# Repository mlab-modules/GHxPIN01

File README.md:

# GHxPIN01 Module: MLAB to PixHawk xPIN interface

## Overview
The GHxPIN01 Module is a pin-header adapter that converts JST-GH connectors, commonly used in [PixHawk](https://github.com/pixhawk/Pixhawk-Standards/blob/master/DS-009%20Pixhawk%20Connector%20Standard.pdf) avionics, to standard pin headers. This module includes 3 to 10pin JST-GH connectors and supports UART, GPS or SPI bus communication, making it a versatile and essential component in the MLAB system for integrating various electronic devices.

## Features
- **User-Friendly Design**: Simplifies connections without complex modifications.
- **High Compatibility**: Integrates seamlessly with MLAB modular components.
- **Durable Construction**: High-quality materials for reliable and robust performance.

## Specifications
- **Connector JST-GH**: 4-10-pin JST-GH [PixHawk standard](https://github.com/pixhawk/Pixhawk-Standards/blob/master/DS-009%20Pixhawk%20Connector%20Standard.pdf)
- **Connector HEADER**: Standard 2.54mm pin header
- **Operating Temperature Range**: -40°C to 85°C

## Possible uses
- Integrating custom avionics into Pixhawk drone projects.
- Connecting JST-GH devices to MLAB standard pin header-based systems.
- Prototyping and development with MLAB modular components.

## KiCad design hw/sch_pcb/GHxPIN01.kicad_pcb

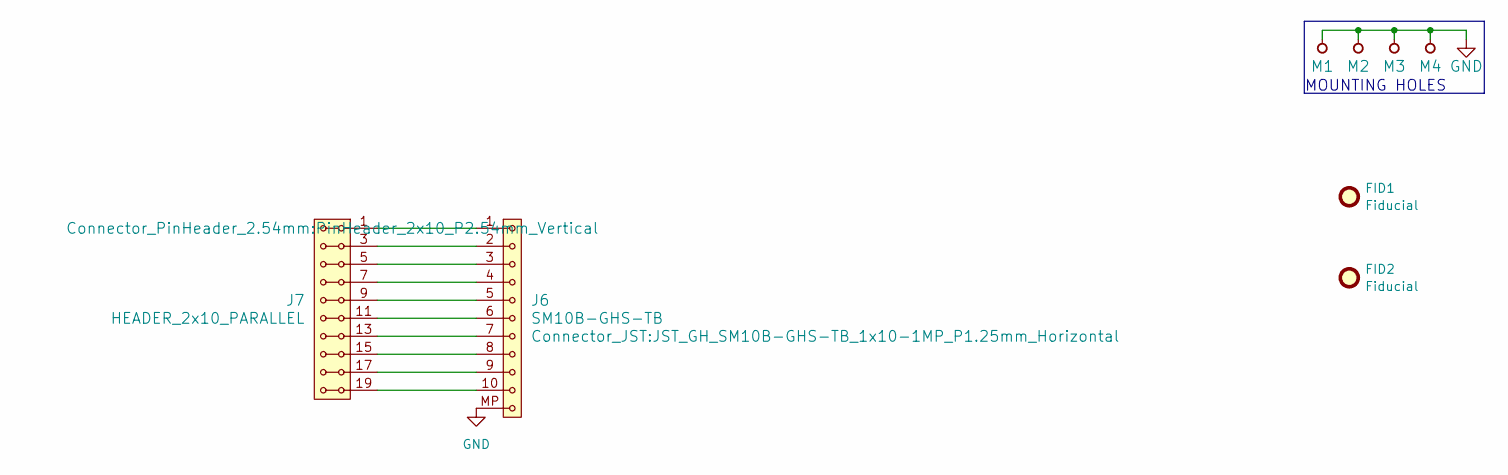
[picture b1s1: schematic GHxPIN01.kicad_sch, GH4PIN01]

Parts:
FID1, FID2: Fiducial; Fiducial_1mm_Mask2mm
J6: SM10B-GHS-TB; JST_GH_SM10B-GHS-TB_1x10-1MP_P1.25mm_Horizontal
J7: HEADER_2x10_PARALLEL; PinHeader_2x10_P2.54mm_Vertical
M1, M2: HOLE M3; MountingHole_3mm
M3, M4: HOLE; MountingHole_3mm

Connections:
GND: J6.MP, M1.1, M2.1, M3.1, M4.1
unnamed: J6.1, J7.1, J7.2
unnamed: J6.2, J7.3, J7.4
unnamed: J6.3, J7.5, J7.6
unnamed: J6.4, J7.7, J7.8
unnamed: J6.5, J7.9, J7.10
unnamed: J6.6, J7.11, J7.12
unnamed: J6.7, J7.13, J7.14
unnamed: J6.8, J7.15, J7.16
unnamed: J6.9, J7.17, J7.18
unnamed: J6.10, J7.19, J7.20

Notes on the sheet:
MOUNTING HOLES

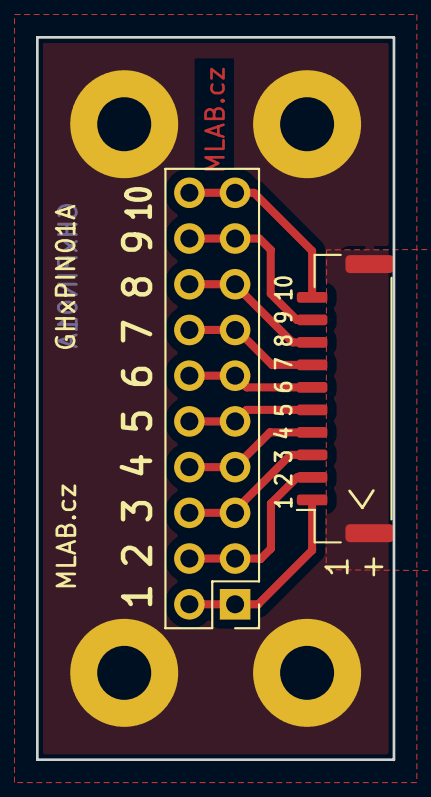
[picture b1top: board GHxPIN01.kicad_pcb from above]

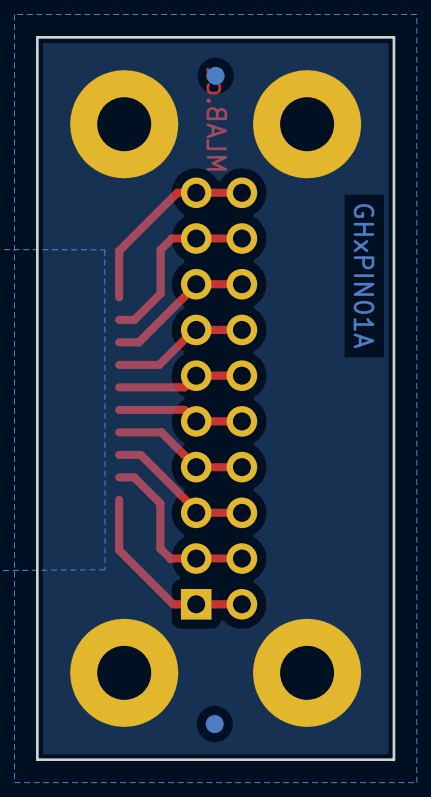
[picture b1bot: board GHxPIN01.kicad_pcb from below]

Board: 2 copper layers, 19.8 x 40.1 mm, 8 parts (2 on the bottom side), 11 nets.

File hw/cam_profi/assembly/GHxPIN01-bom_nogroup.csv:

Component,Description,Part,References,Value,Footprint,Quantity Per PCB,Datasheet
1,"2x10 2.54 mm pitch header, 2 pins next to each other are connected",HEADER_2x10_PARALLEL,J7,HEADER_2x10_PARALLEL,PinHeader_2x10_P2.54mm_Vertical,1,
2,"Zásuvka; kabel-pl.spoj; vidlice; GH; 1,25mm; PIN: 10; SMT; 50V; 1A",SM10B-GHS-TB,J6,SM10B-GHS-TB,JST_GH_SM10B-GHS-TB_1x10-1MP_P1.25mm_Horizontal,1,

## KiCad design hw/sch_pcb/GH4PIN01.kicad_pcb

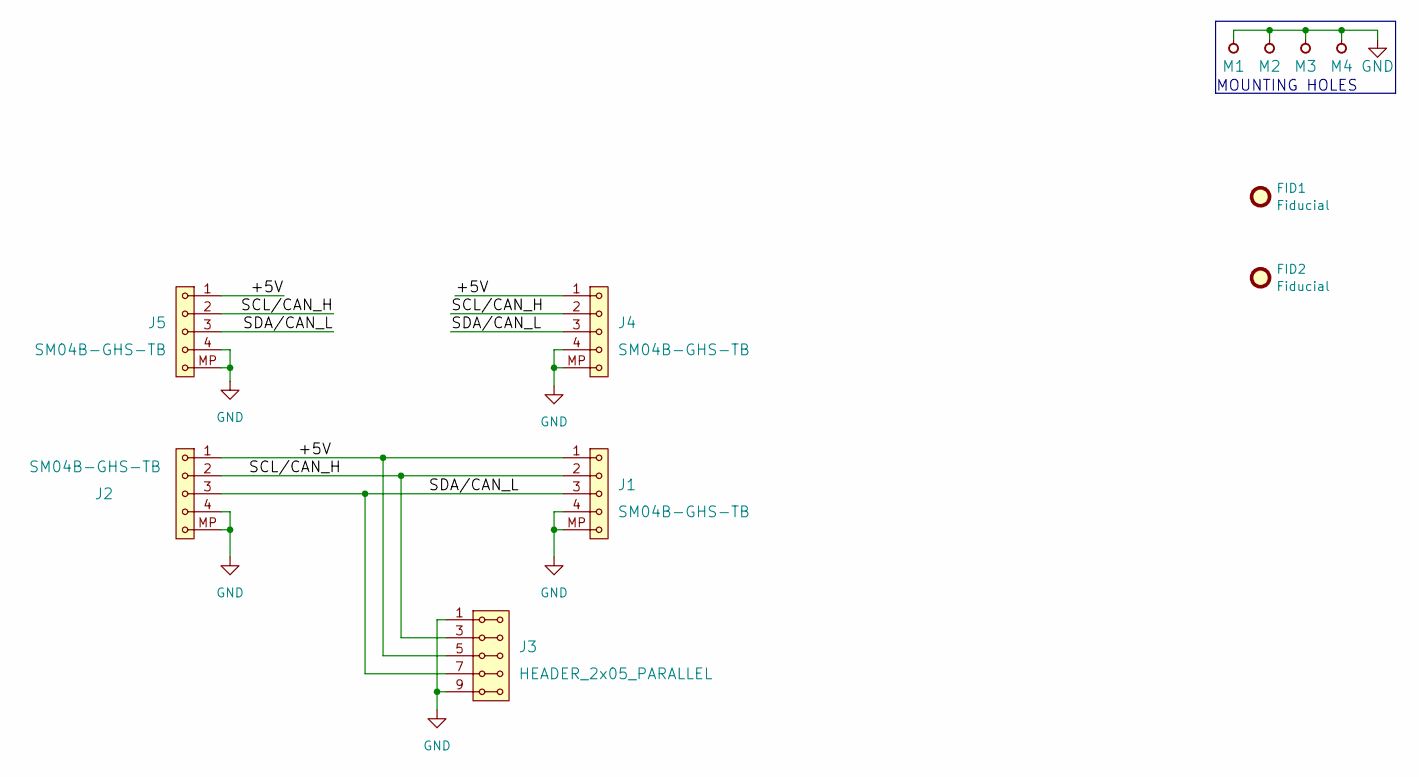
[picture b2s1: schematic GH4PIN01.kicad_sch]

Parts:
FID1, FID2: Fiducial; Fiducial_1mm_Mask2mm
J1, J2, J4, J5: SM04B-GHS-TB; JST_GH_SM04B-GHS-TB_1x04-1MP_P1.25mm_Horizontal
J3: HEADER_2x05_PARALLEL; Straight_2x05
M1, M2: HOLE M3; MountingHole_3mm
M3, M4: HOLE; MountingHole_3mm

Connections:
/+5V: J1.1, J2.1, J3.5, J3.6, J4.1, J5.1
/SCL/CAN_H: J1.2, J2.2, J3.3, J3.4, J4.2, J5.2
/SDA/CAN_L: J1.3, J2.3, J3.7, J3.8, J4.3, J5.3
GND: J1.4, J1.MP, J2.4, J2.MP, J3.1, J3.2, J3.9, J3.10, J4.4, J4.MP, J5.4, J5.MP, M1.1, M2.1, M3.1, M4.1

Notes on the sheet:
MOUNTING HOLES

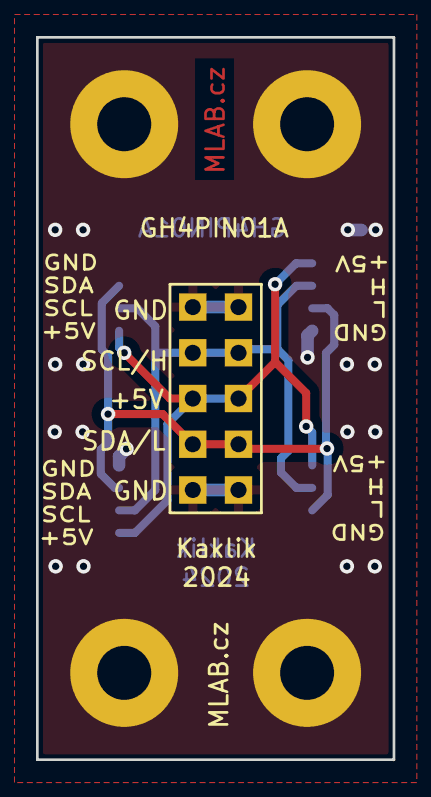
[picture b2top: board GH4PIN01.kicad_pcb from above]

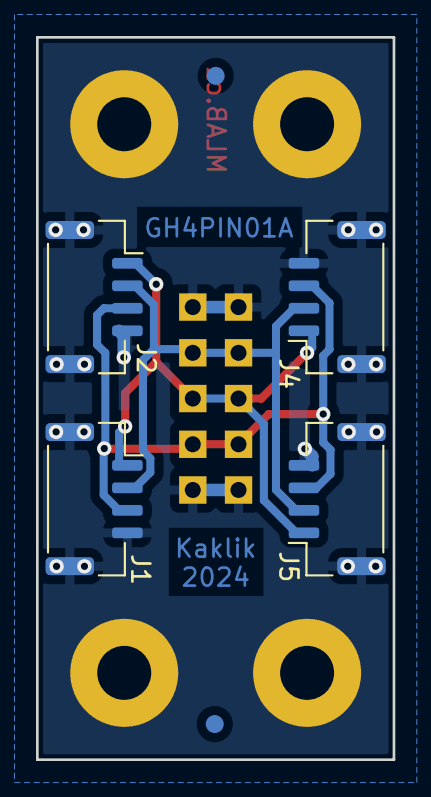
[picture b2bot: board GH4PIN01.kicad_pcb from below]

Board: 2 copper layers, 19.8 x 40.1 mm, 11 parts (6 on the bottom side), 4 nets.

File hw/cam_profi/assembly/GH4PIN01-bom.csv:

Component,Description,Part,References,Value,Footprint,Quantity Per PCB,Datasheet
1,"2x05 2.54 mm pitch header, 2 pins next to each other are connected",HEADER_2x05_PARALLEL,J3,HEADER_2x05_PARALLEL,Straight_2x05,1,
2,,SM04B-GHS-TB,J1J2,SM04B-GHS-TB,JST_GH_SM04B-GHS-TB_1x04-1MP_P1.25mm_Horizontal,2,

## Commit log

2023-02-09 test coomit
2023-02-09 init workflou
2023-02-09 My first module
2023-05-25 automated commit; add github actions
2023-05-25 Update metadata files
2023-05-25 Update actions products
2023-05-28 Update workflow files
2023-07-01 Cleanup and save in KiCAD 7.
2023-07-05 automated commit; rename source files to new naming convence
2023-09-16 Update image to image_title
2023-09-16 Update status
2024-05-30 The routed layout.
2024-05-30 Improve manufacturing texts.
2024-06-05 Add labels for CAN bus.
2024-06-06 Move the connectors more inside to PCB.
2024-06-06 Modify board clearance setup.
2024-11-07 initial version of GHxPIN module
2024-11-07 update pcb
2024-11-07 update assets
2025-06-05 Update documentation and photos.
